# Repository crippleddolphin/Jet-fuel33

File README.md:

# Jet-fuel33
https://i.imgur.com/FCYjS9T.jpg

# Intro
This is the github page for the Jet Fuel33, a 3x11 ortholinear keyboard that is compatible with alps and mx switches, it also features usb-c.
the layout in this repo is my personal one which is made for use with swerty, although all the files necessary to make your own are available here too.

# Description
My goal with this project was to create the ideal keyboard for me, ever since i got started with the custom keyboard "hobby" i have always been eyeing small keyboards (40% size or smaller). The first custom keyboard i bought was an Orthodox, wich is a 40% split ortholinear ergonomic keyboard. after some consideration i decided that 3x11 would be the optimal layout for me, and since i did not find any existing designs that were 3x11 and used USB-C i decided to design my own keyboard. after teaching myself how to use the pcb design program Kicad i also figured out how to design parts for laser cutting, as that was the method i decided to use for making the case. The original idea was to use a case made out of 5 3mm thick layers of clear acrylic with some standoffs and screws to hold it together. But after making the first prototype i realised that using just 4 layers is possible with some slight modifications to the bottom plate, the modification in question was cutting out a small notch beneath where the usb port is located, otherwise the port gets a bit squished. Making the case have 3mm less room inside which makes it sound slightly better. I have also made one keyboard with a case made out of 3mm thick pieces of high grade birch plywood that were glued together permanently. The use of plywood greatly improves the sound when typing in my opinion.

# Features
- 3x11 ortholinear layout.

- Uses an Atmega32u4 microcontroller.

- Overcurrent, ESD and reverse polarity protection.

- USB Type-C 2.0 port.

- Both MX and Alps compatible.

- QMK powered

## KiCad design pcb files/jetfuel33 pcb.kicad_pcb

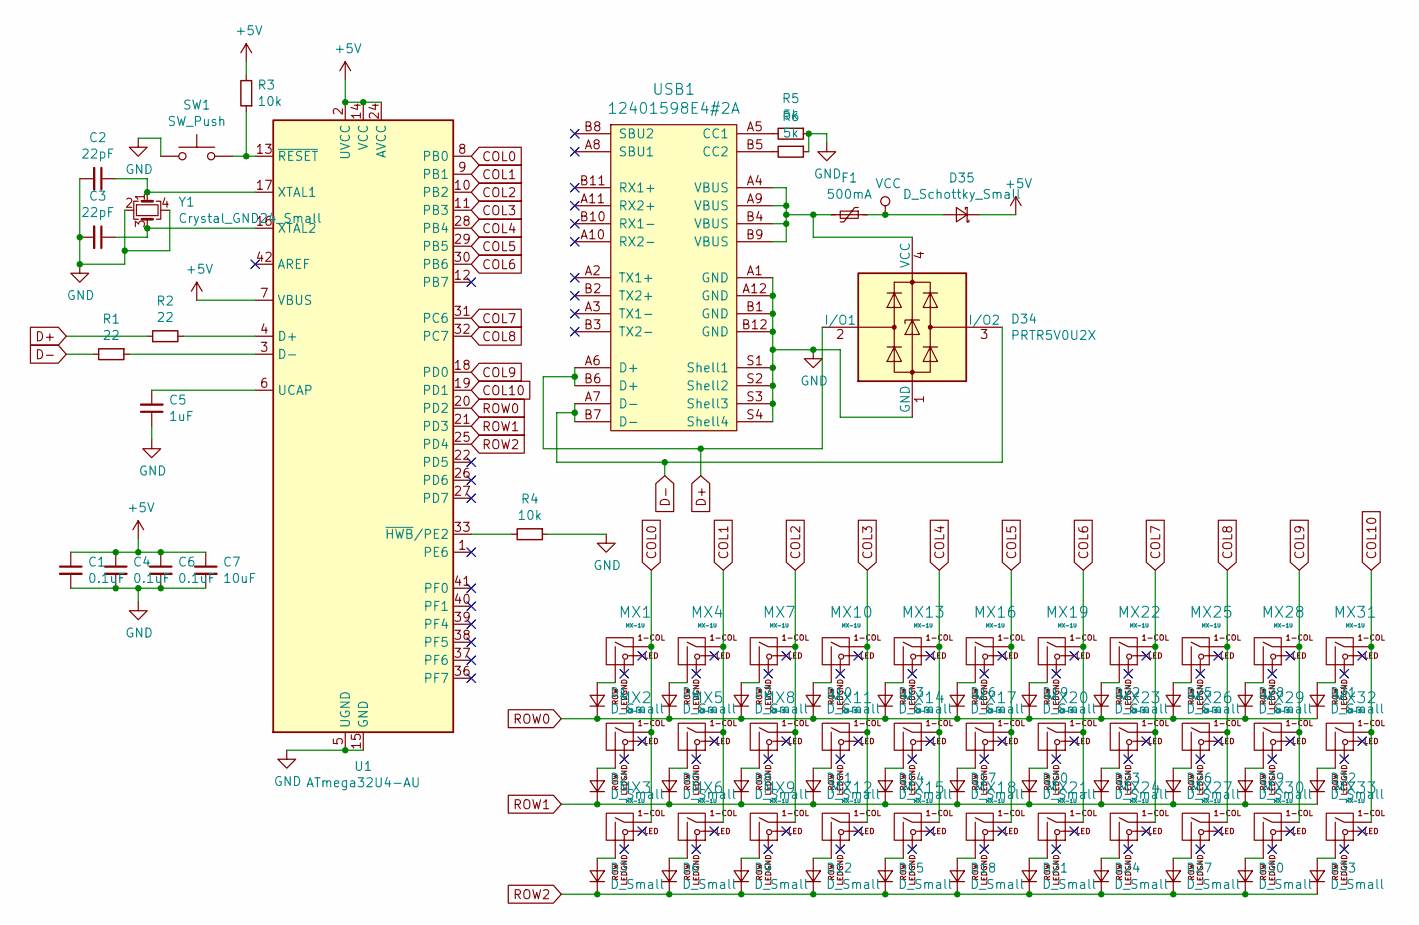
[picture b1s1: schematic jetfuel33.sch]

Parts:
C1, C4, C6: 0.1uF; C_0805_2012Metric
C2, C3: 22pF; C_0805_2012Metric
C5: 1uF; C_0805_2012Metric
C7: 10uF; C_0805_2012Metric
D1, D2, D3, D4, D5, D6, D7, D8, D9, D10, D11, D12, D13, D14, D15, D16, D17, D18, D19, D20, D21, D22, D23, D24, D25, D26, D27, D28, D29, D30, D31, D32, D33: D_Small; D_SOD-123
D34: PRTR5V0U2X; SOT-143
D35: D_Schottky_Small; D_SOD-123
F1: 500mA; Fuse_1206_3216Metric_Pad1.42x1.75mm_HandSolder
MX1, MX2, MX3, MX4, MX5, MX6, MX7, MX8, MX9, MX10, MX11, MX12, MX13, MX14, MX15, MX16, MX17, MX18, MX19, MX20, MX21, MX22, MX23, MX24, MX25, MX26, MX27, MX28, MX29, MX30, MX31, MX32, MX33: MX-1U; MX-1U-NoLED
R1, R2: 22; R_0805_2012Metric
R3, R4: 10k; R_0805_2012Metric
R5, R6: 5k; R_0805_2012Metric
SW1: SW_Push; SKQG-1155865
U1: ATmega32U4-AU; TQFP-44_10x10mm_P0.8mm
USB1: 12401598E4#2A
Y1: Crystal_GND24_Small; Crystal_SMD_3225-4Pin_3.2x2.5mm

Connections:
+5V: C1.1, C4.1, C6.1, C7.1, D35.1 (K), R3.2, U1.2 (UVCC), U1.7 (VBUS), U1.14 (VCC), U1.24 (AVCC), U1.34 (VCC), U1.44 (AVCC)
COL0: MX1.1 (COL), MX2.1 (COL), MX3.1 (COL), U1.8 (PB0)
COL1: MX4.1 (COL), MX5.1 (COL), MX6.1 (COL), U1.9 (PB1)
COL2: MX7.1 (COL), MX8.1 (COL), MX9.1 (COL), U1.10 (PB2)
COL3: MX10.1 (COL), MX11.1 (COL), MX12.1 (COL), U1.11 (PB3)
COL4: MX13.1 (COL), MX14.1 (COL), MX15.1 (COL), U1.28 (PB4)
COL5: MX16.1 (COL), MX17.1 (COL), MX18.1 (COL), U1.29 (PB5)
COL6: MX19.1 (COL), MX20.1 (COL), MX21.1 (COL), U1.30 (PB6)
COL7: MX22.1 (COL), MX23.1 (COL), MX24.1 (COL), U1.31 (PC6)
COL8: MX25.1 (COL), MX26.1 (COL), MX27.1 (COL), U1.32 (PC7)
COL9: MX28.1 (COL), MX29.1 (COL), MX30.1 (COL), U1.18 (PD0)
COL10: MX31.1 (COL), MX32.1 (COL), MX33.1 (COL), U1.19 (PD1)
D+: D34.2 (I/O1), R2.1, USB1.A6 (D+), USB1.B6 (D+); also elsewhere on the board
D-: D34.3 (I/O2), R1.2, USB1.A7 (D-), USB1.B7 (D-); also elsewhere on the board
GND: C1.2, C2.2, C3.2, C4.2, C5.1, C6.2, C7.2, D34.1 (GND), R4.1, R5.1, R6.1, SW1.1, U1.5 (UGND), U1.15 (GND), U1.23 (GND), U1.35 (GND), U1.43 (GND), USB1.A1 (GND), USB1.A12 (GND), USB1.B1 (GND), USB1.B12 (GND), USB1.S1 (Shell1), USB1.S2 (Shell2), USB1.S3 (Shell3), USB1.S4 (Shell4), Y1.2, Y1.4; also elsewhere on the board
unnamed: C2.1, U1.17 (XTAL1), Y1.1
unnamed: C3.1, U1.16 (XTAL2), Y1.3
unnamed: C5.2, U1.6 (UCAP)
unnamed: D1.2 (A), MX1.2 (ROW)
unnamed: D2.2 (A), MX2.2 (ROW)
unnamed: D3.2 (A), MX3.2 (ROW)
unnamed: D4.2 (A), MX4.2 (ROW)
unnamed: D5.2 (A), MX5.2 (ROW)
unnamed: D6.2 (A), MX6.2 (ROW)
unnamed: D7.2 (A), MX7.2 (ROW)
unnamed: D8.2 (A), MX8.2 (ROW)
unnamed: D9.2 (A), MX9.2 (ROW)
unnamed: D10.2 (A), MX10.2 (ROW)
unnamed: D11.2 (A), MX11.2 (ROW)
unnamed: D12.2 (A), MX12.2 (ROW)
unnamed: D13.2 (A), MX13.2 (ROW)
unnamed: D14.2 (A), MX14.2 (ROW)
unnamed: D15.2 (A), MX15.2 (ROW)
unnamed: D16.2 (A), MX16.2 (ROW)
unnamed: D17.2 (A), MX17.2 (ROW)
unnamed: D18.2 (A), MX18.2 (ROW)
unnamed: D19.2 (A), MX19.2 (ROW)
unnamed: D20.2 (A), MX20.2 (ROW)
unnamed: D21.2 (A), MX21.2 (ROW)
unnamed: D22.2 (A), MX22.2 (ROW)
unnamed: D23.2 (A), MX23.2 (ROW)
unnamed: D24.2 (A), MX24.2 (ROW)
unnamed: D25.2 (A), MX25.2 (ROW)
unnamed: D26.2 (A), MX26.2 (ROW)
unnamed: D27.2 (A), MX27.2 (ROW)
unnamed: D28.2 (A), MX28.2 (ROW)
unnamed: D29.2 (A), MX29.2 (ROW)
unnamed: D30.2 (A), MX30.2 (ROW)
unnamed: D31.2 (A), MX31.2 (ROW)
unnamed: D32.2 (A), MX32.2 (ROW)
unnamed: D33.2 (A), MX33.2 (ROW)
unnamed 51: D34.4 (VCC), F1.2, USB1.A4 (VBUS), USB1.A9 (VBUS), USB1.B4 (VBUS), USB1.B9 (VBUS); also elsewhere on the board
unnamed: R1.1, U1.3 (D-)
unnamed: R2.2, U1.4 (D+)
unnamed: R3.1, SW1.2, U1.13 (~RESET)
unnamed: R4.2, U1.33 (~HWB~/PE2)
unnamed 56: R5.2, USB1.A5 (CC1); also elsewhere on the board
unnamed 57: R6.2, USB1.B5 (CC2); also elsewhere on the board
ROW0: D1.1 (K), D4.1 (K), D7.1 (K), D10.1 (K), D13.1 (K), D16.1 (K), D19.1 (K), D22.1 (K), D25.1 (K), D28.1 (K), D31.1 (K), U1.20 (PD2)
ROW1: D2.1 (K), D5.1 (K), D8.1 (K), D11.1 (K), D14.1 (K), D17.1 (K), D20.1 (K), D23.1 (K), D26.1 (K), D29.1 (K), D32.1 (K), U1.21 (PD3)
ROW2: D3.1 (K), D6.1 (K), D9.1 (K), D12.1 (K), D15.1 (K), D18.1 (K), D21.1 (K), D24.1 (K), D27.1 (K), D30.1 (K), D33.1 (K), U1.25 (PD4)
VCC: D35.2 (A), F1.1

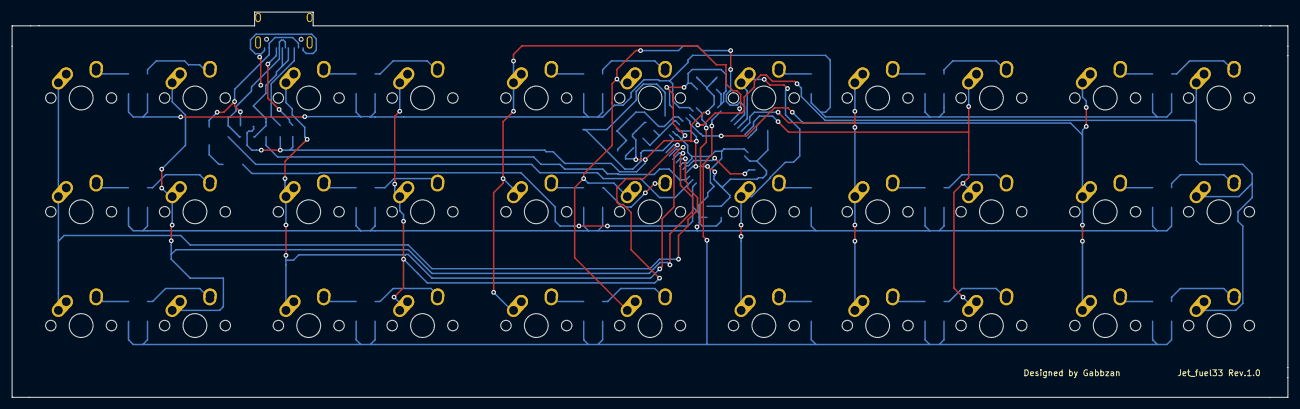
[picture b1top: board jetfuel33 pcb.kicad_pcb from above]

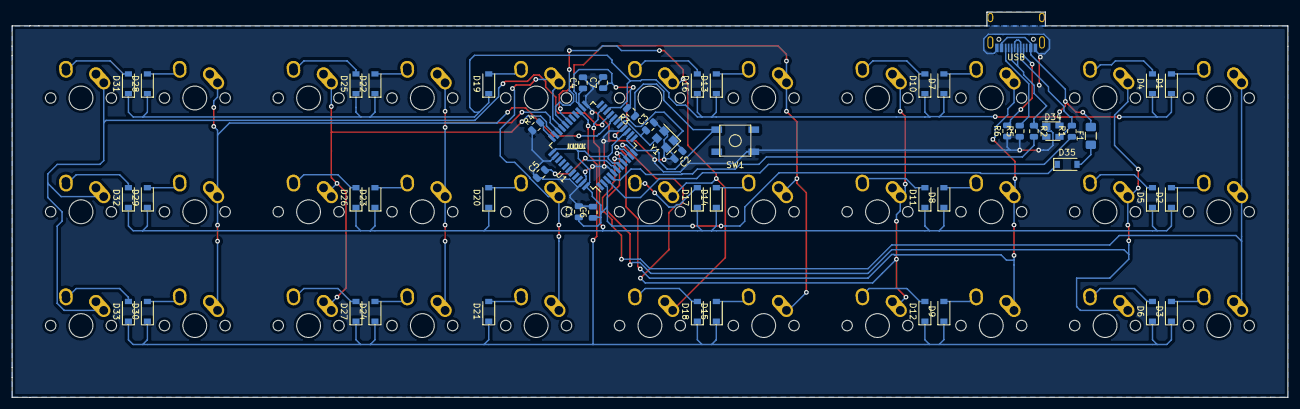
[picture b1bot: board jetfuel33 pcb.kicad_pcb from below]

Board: 2 copper layers, 213.6 x 64.5 mm, 86 parts (53 on the bottom side), 62 nets.

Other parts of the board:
USB: HRO-TYPE-C-31-M-12

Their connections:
D+: USB.6, USB.8; also elsewhere on the board
D-: USB.5, USB.7; also elsewhere on the board
GND: USB.1, USB.12; also elsewhere on the board
unnamed 51: USB.2, USB.11; also elsewhere on the board
unnamed 56: USB.10; also elsewhere on the board
unnamed 57: USB.4; also elsewhere on the board

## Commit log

2019-05-25 Create qmk files
2019-05-25 Create config
2019-05-26 Create LICENSE
2021-06-02 Create pcb files
2021-06-02 Create d
